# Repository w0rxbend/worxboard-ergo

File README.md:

# worxboard ergo

A split Planck in one curved shell. Forty-eight 1u keys in two wells, opened ten degrees. A full-width palm rest, a memory LCD between the wells, and three places to plug in one USB-C cable. Cherry MX or Kailh Choc v1.

**[Product page](https://w0rxbend.github.io/worxboard-ergo/)** · **[3D print guide](docs/printing.md)** · **[Releases](https://github.com/w0rxbend/worxboard-ergo/releases)**

> [!WARNING]
> **Revision A0 is an engineering preview.** You can print the case. You cannot order the PCB: it has no copper tracks. No keyboard has been built, and the firmware has never run on a board. The pictures are renders of the design.

## What you can do today

| You want to | Start here | State |
|---|---|---|
| See the design | [Product page](https://w0rxbend.github.io/worxboard-ergo/) | Renders of the CAD model |
| Print the case | [3D print guide](docs/printing.md) | Watertight meshes. Nothing printed yet |
| Mill the case | [CNC traveler](docs/cnc.md) | STEP geometry. No toolpath |
| Read the circuit | [Electrical notes](docs/electrical.md) | Schematic and placed parts. **Zero tracks** |
| Build the firmware | [Firmware notes](docs/firmware.md) | Compiles. Never flashed to hardware |
| Order a PCB | — | **Blocked.** See [verification](docs/verification.md) |

## The design

| | |
|---|---|
| Layout | 48 ortholinear keys, two blocks of 4 × 6, every key 1u. Numbers and F-keys on the Lower layer |
| Shell | 303 × 223 mm. A curved outline, an open slot between the wells, a flush top cover |
| Ergonomics | 10° splay, 67 mm palm rest, flat stance, 6.7° negative tilt on an optional magnetic riser |
| Switches | Cherry MX compatible with a 1.5 mm plate, or Kailh Choc v1 with a 1.2 mm plate. Hot-swap sockets |
| Controller | Bare RP2040 with 16 MiB flash, reset, BOOT, and SWD |
| Cable | Three USB-C positions, one host at a time. No battery, no radio |
| Display | 160 × 68 memory LCD that names the active layer |
| Firmware | ZMK at a pinned revision |

Both wells sit on one flat board, so the keys do not tent. The three USB-C jacks are alternative cable positions, not a hub.

## Print the case

1. Choose [MX](cad/exports/mx) or [Choc v1](cad/exports/choc). The parts do not mix.
2. Choose whole parts (350 mm class bed) or split halves (about 235 mm).
3. Print the four test pieces, then the chassis, plate, top cover, and palm rest.

The full steps, orientation, settings, and screw list are in the [3D print guide](docs/printing.md).

## Repository map

| Path | What it holds |
|---|---|
| [`layout/model.py`](layout/model.py) | Source of truth for key positions, key order, and shared holes |
| [`cad/model.py`](cad/model.py) | Parametric case model (build123d) |
| [`cad/exports/`](cad/exports) | STEP, STL, 3MF, and FreeCAD files for both switch families |
| [`pcb/`](pcb) | KiCad 10 projects, generator scripts, ERC and DRC reports |
| [`firmware/`](firmware) | ZMK board definition, USB port selector, compiled UF2 |
| [`site/`](site) | Product page, published with GitHub Pages |
| [`docs/`](docs/README.md) | Guides, design record, verification, roadmap |
| [`tools/`](tools) | Generators and checks behind the `make` targets |
| [`tests/`](tests) | Geometry and contract tests |

## Reproduce the files

Install [uv](https://docs.astral.sh/uv/), Docker, and FreeCAD 1.1.x.

```sh
git clone --recurse-submodules https://github.com/w0rxbend/worxboard-ergo.git
cd worxboard-ergo
uv sync --locked
make generate       # layout drawing and ZMK keymap
make cad            # STEP, STL, 3MF, solid and fit checks
make native         # FreeCAD save and reopen
make test
make pcb            # KiCad boards and ERC/DRC reports. Does not route
make firmware       # pinned ZMK image
make manifest       # checksums
make check-fabrication   # fails on purpose at A0
```

`make check-fabrication` stays red until both boards are routed, reviewed, and tested on hardware. Tool versions are pinned in [`toolchain.lock.json`](toolchain.lock.json) and `uv.lock`.

To redraw the product renders (Blender's path tracer as a Python module, about 30 minutes on 16 CPU threads) and the laser artwork for the signature:

```sh
uv run --no-project --python 3.13 --with bpy==5.3.0 --with build123d==0.13.0 \
    --with shapely==2.2.0 --with pillow==13.0.0 --with imagequant==1.1.6 python -m tools.render
make laser
```

## Status and next steps

The next gate is [A1, electrical and mechanical review](docs/roadmap.md). The main open work:

- Route both PCBs. Turn the USB jacks to face the rear wall and move the parts that sit under the plate.
- Print the test pieces and measure them.
- Review USB power and the J6/J7 flashing override on real hardware.

The evidence for every claim is in [verification](docs/verification.md). Changes per release are in the [changelog](CHANGELOG.md).

## License

Original project work is GPL-3.0-or-later. ZMK, the reference tree, and third-party footprints keep their own notices. See [THIRD_PARTY.md](THIRD_PARTY.md).

This is an independent project. It is not affiliated with Microsoft, System76, or OLKB. The [System76 Launch](https://github.com/system76/launch) tree is a pinned [reference submodule](references/system76-launch); [feature coverage](docs/launch-coverage.md) records the differences.

The product page sets [Outfit](https://github.com/Outfitio/Outfit-Fonts) under the SIL Open Font License. The license text ships in [site/fonts](site/fonts).

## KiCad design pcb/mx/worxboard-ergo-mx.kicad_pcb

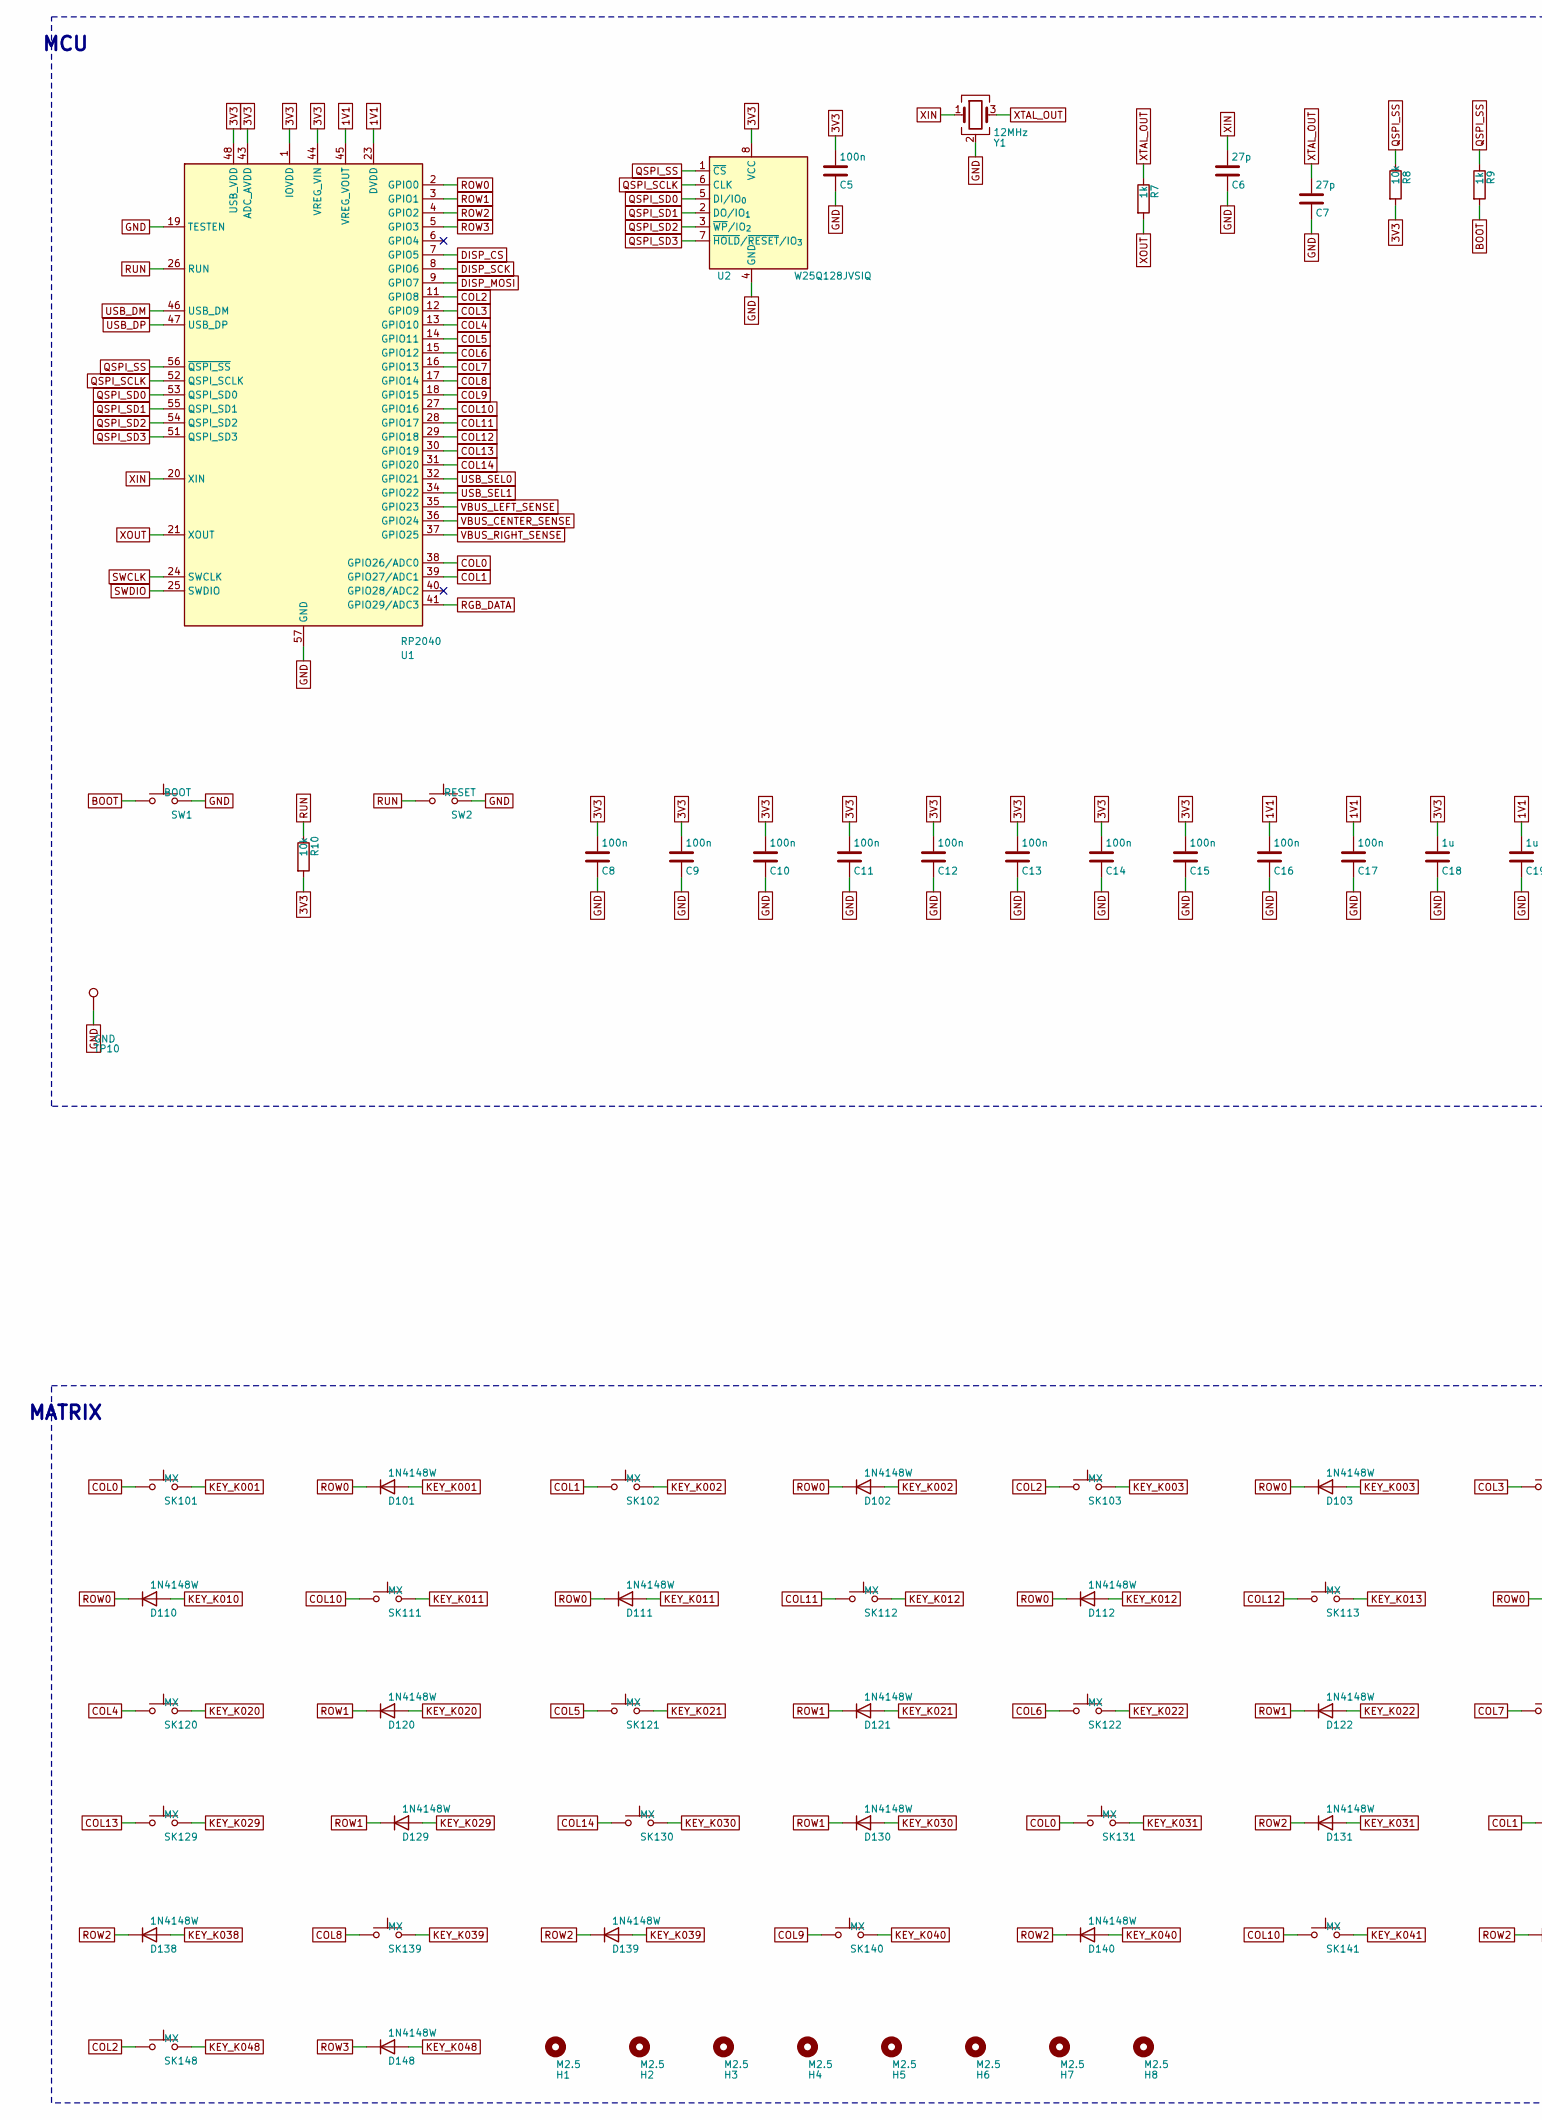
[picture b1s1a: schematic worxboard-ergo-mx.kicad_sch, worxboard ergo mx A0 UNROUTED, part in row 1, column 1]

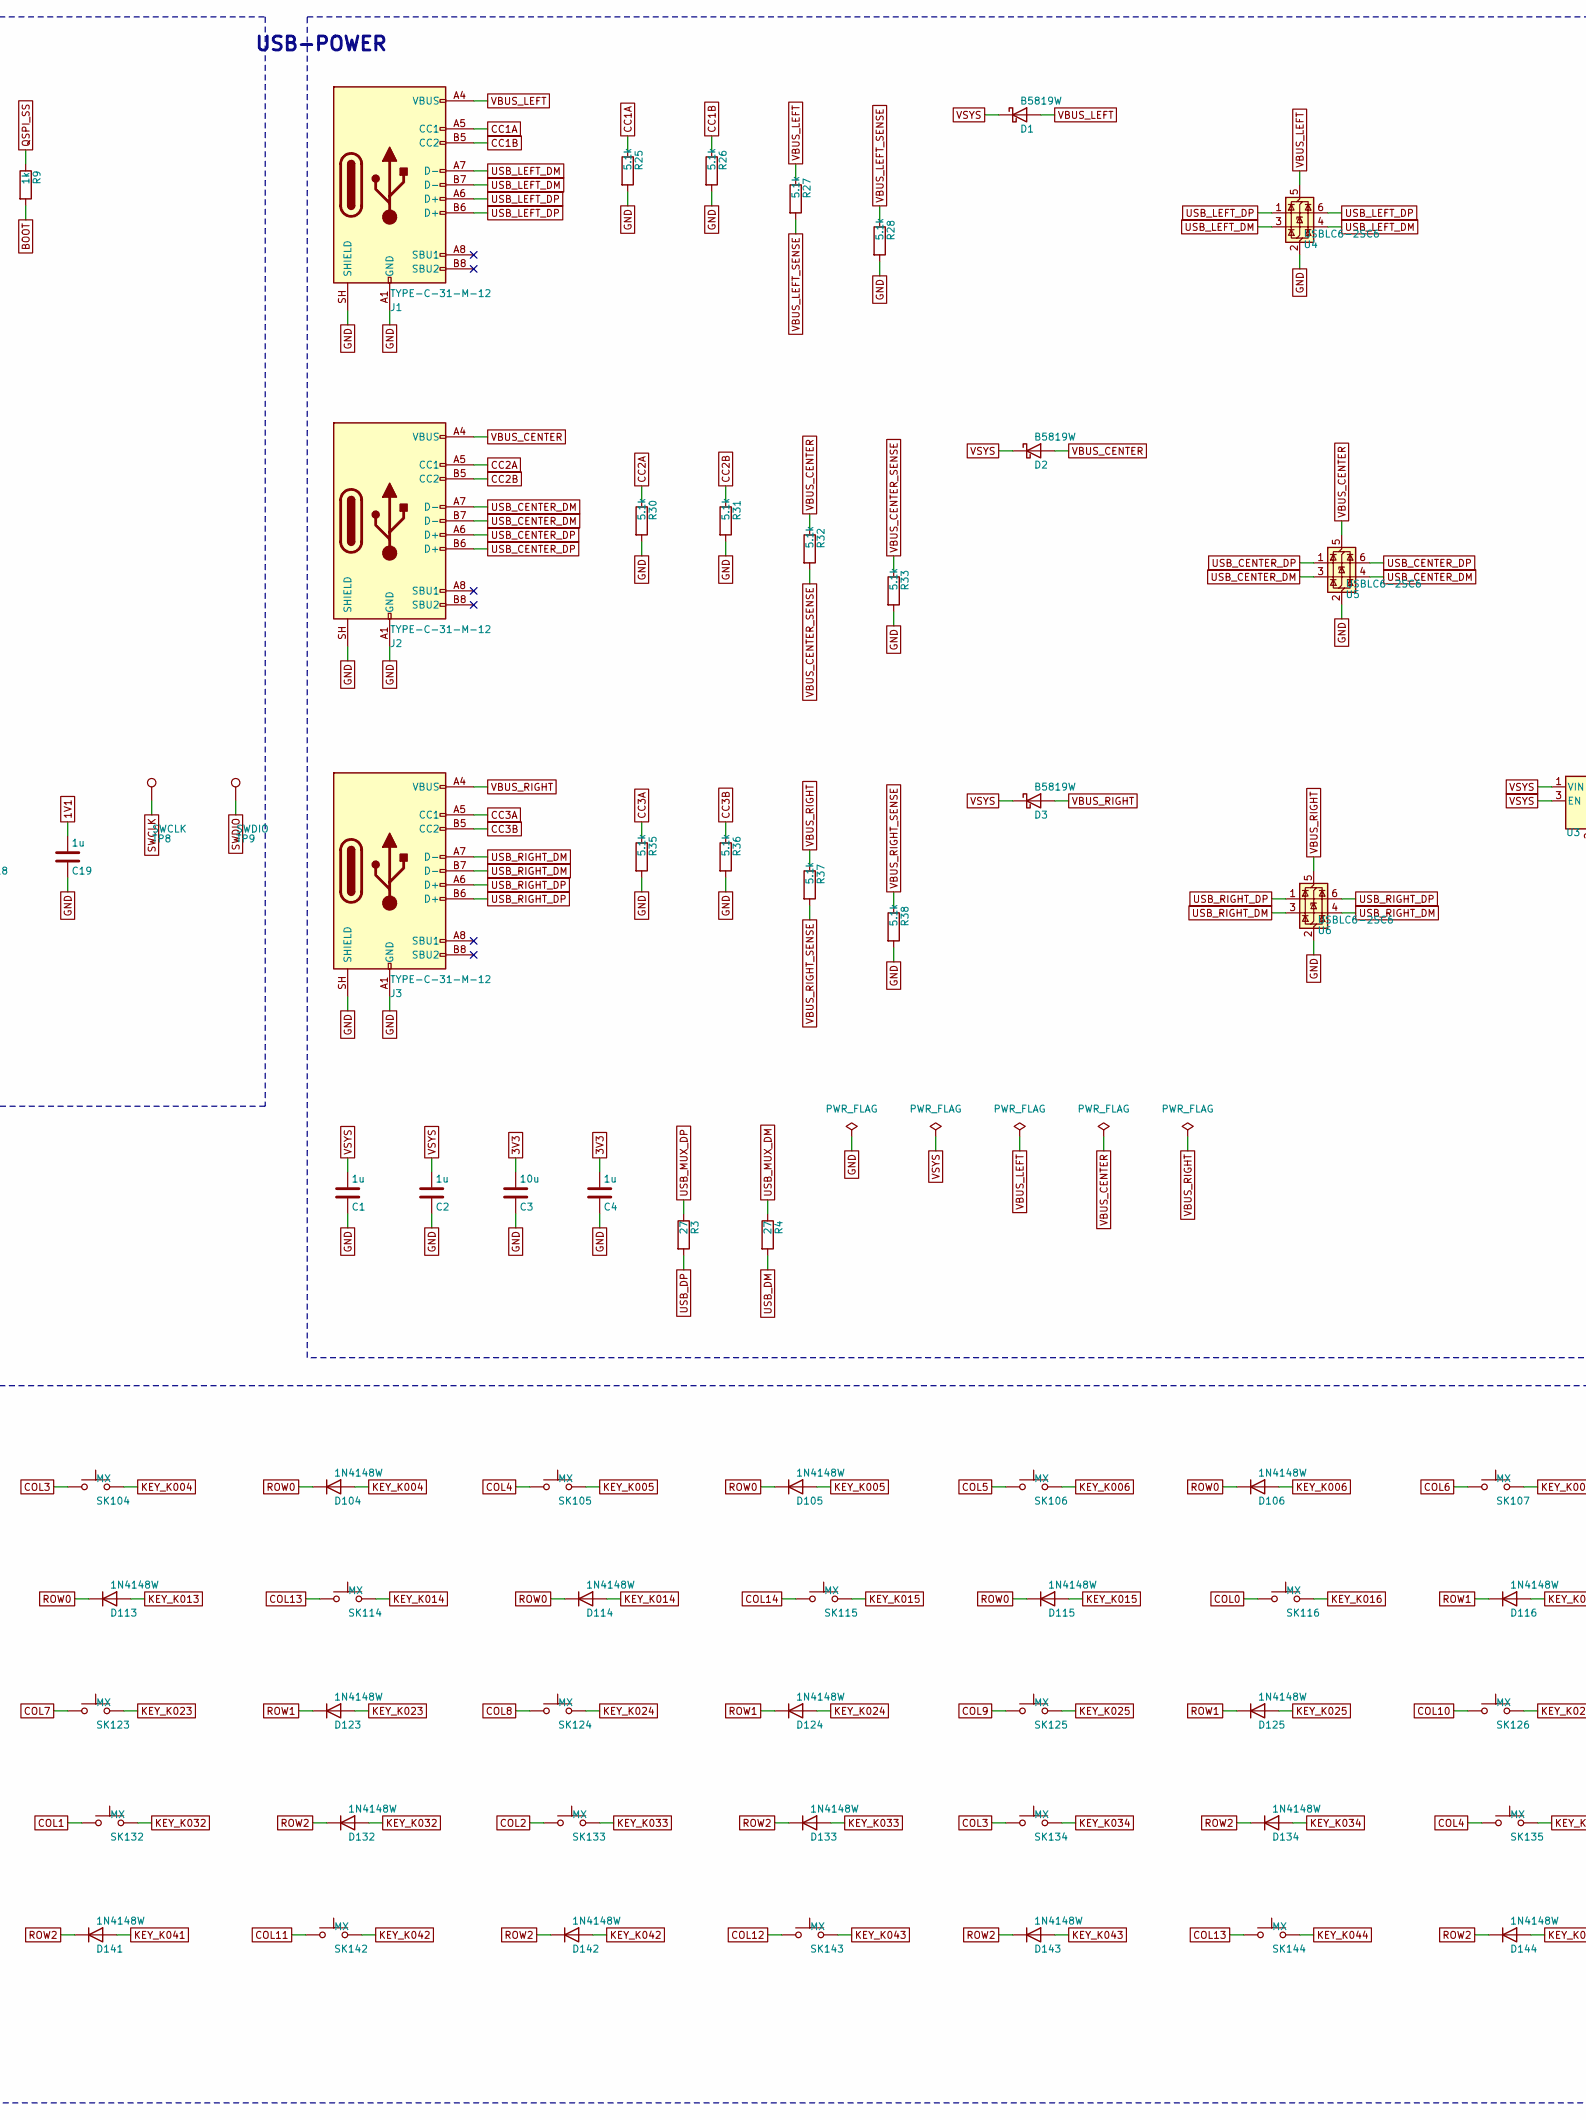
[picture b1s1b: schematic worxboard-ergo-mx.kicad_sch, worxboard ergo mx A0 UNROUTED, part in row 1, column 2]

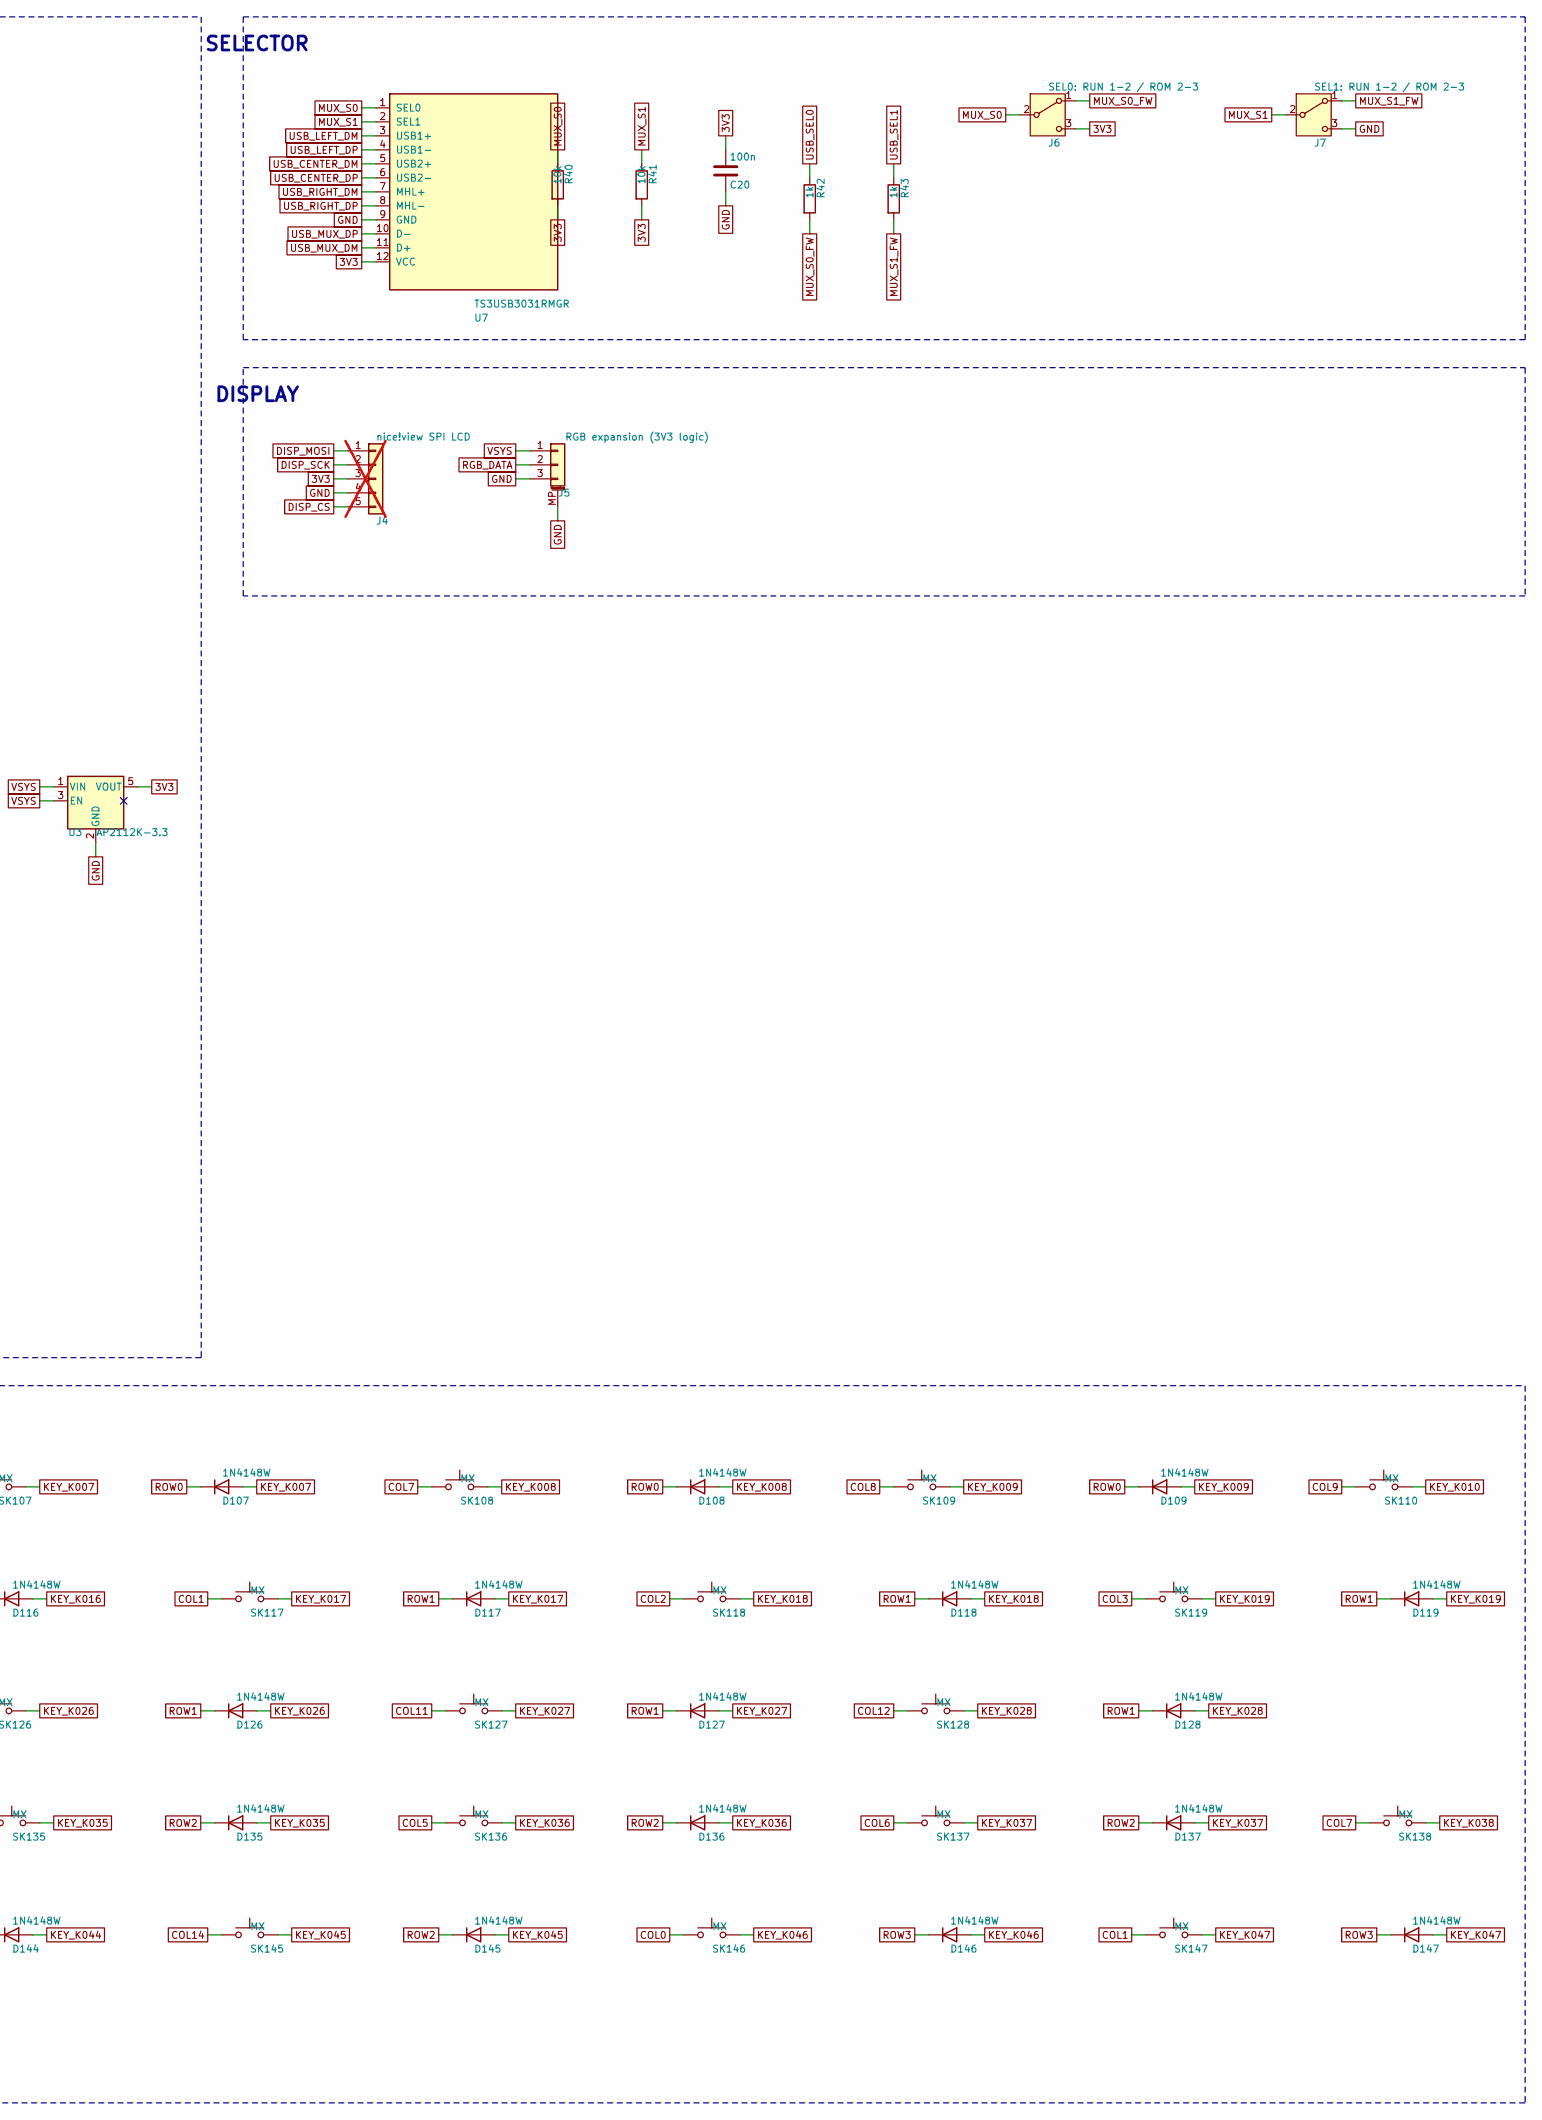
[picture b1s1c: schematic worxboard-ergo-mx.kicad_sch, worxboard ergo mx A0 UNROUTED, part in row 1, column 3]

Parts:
C1, C2, C4, C18, C19: 1u; C_0402_1005Metric; LCSC C52923
C3: 10u; C_0402_1005Metric; LCSC C15525
C5, C8, C9, C10, C11, C12, C13, C14, C15, C16, C17, C20: 100n; C_0402_1005Metric; LCSC C1525
C6, C7: 27p; C_0402_1005Metric; LCSC C1557
D1, D2, D3: B5819W; D_SOD-123; LCSC C8598
D101, D102, D103, D104, D105, D106, D107, D108, D109, D110, D111, D112, D113, D114, D115, D116, D117, D118, D119, D120, D121, D122, D123, D124, D125, D126, D127, D128, D129, D130, D131, D132, D133, D134, D135, D136, D137, D138, D139, D140, D141, D142, D143, D144, D145, D146, D147, D148: 1N4148W; D_SOD-123; LCSC C81598
H1, H2, H3, H4, H5, H6, H7, H8: M2.5; MountingHole_2.7mm_M2.5
J1, J2, J3: TYPE-C-31-M-12; USB_C_Receptacle_HRO_TYPE-C-31-M-12; LCSC C165948
J4: nice!view SPI LCD; PinSocket_1x05_P2.54mm_Vertical_H5.0mm; not fitted
J5: RGB expansion (3V3 logic); JST_SH_SM03B-SRSS-TB_1x03-1MP_P1.00mm_Horizontal; LCSC C160403
J6: SEL0: RUN 1-2 / ROM 2-3; SW_SPDT_PCM12; LCSC C221841
J7: SEL1: RUN 1-2 / ROM 2-3; SW_SPDT_PCM12; LCSC C221841
R3, R4: 27; R_0402_1005Metric; LCSC C2909343
R7, R9, R42, R43: 1k; R_0402_1005Metric; LCSC C11702
R8, R10, R40, R41: 10k; R_0402_1005Metric; LCSC C25744
R25, R26, R27, R28, R30, R31, R32, R33, R35, R36, R37, R38: 5.1k; R_0402_1005Metric; LCSC C25905
SK101, SK102, SK103, SK104, SK105, SK106, SK107, SK108, SK109, SK110, SK111, SK112, SK113, SK114, SK115, SK116, SK117, SK118, SK119, SK120, SK121, SK122, SK123, SK124, SK125, SK126, SK127, SK128, SK129, SK130, SK131, SK132, SK133, SK134, SK135, SK136, SK137, SK138, SK139, SK140, SK141, SK142, SK143, SK144, SK145, SK146, SK147, SK148: MX; SW_MX_Hotswap_Kailh; LCSC C2803348
SW1: BOOT; SW_SPST_TS-1088-xR020; LCSC C455280
SW2: RESET; SW_SPST_TS-1088-xR020; LCSC C455280
TP8: SWCLK; TestPoint_Pad_D1.0mm
TP9: SWDIO; TestPoint_Pad_D1.0mm
TP10: GND; TestPoint_Pad_D1.0mm
U1: RP2040; QFN-56-1EP_7x7mm_P0.4mm_EP3.2x3.2mm; LCSC C2040
U2: W25Q128JVSIQ; SOIC-8_5.3x5.3mm_P1.27mm; LCSC C97521
U3: AP2112K-3.3; SOT-23-5; LCSC C51118
U4, U5, U6: USBLC6-2SC6; SOT-23-6; LCSC C7519
U7: TS3USB3031RMGR; Texas_RMG0012A_WQFN-12_1.8x1.8mm_P0.4mm; LCSC C2652459
Y1: 12MHz; Crystal_SMD_3225-4Pin_3.2x2.5mm; LCSC C49304726

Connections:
1V1: C16.1, C17.1, C19.1, U1.23 (DVDD), U1.45 (VREG_VOUT), U1.50 (DVDD)
3V3: C3.1, C4.1, C5.1, C8.1, C9.1, C10.1, C11.1, C12.1, C13.1, C14.1, C15.1, C18.1, C20.1, J4.3, J6.3 (C), R8.2, R10.2, R40.2, R41.2, U1.1 (IOVDD), U1.10 (IOVDD), U1.22 (IOVDD), U1.33 (IOVDD), U1.42 (IOVDD), U1.43 (ADC_AVDD), U1.44 (VREG_VIN), U1.48 (USB_VDD), U1.49 (IOVDD), U2.8 (VCC), U3.5 (VOUT), U7.12 (VCC)
BOOT: R9.2, SW1.1
CC1A: J1.A5 (CC1), R25.1
CC1B: J1.B5 (CC2), R26.1
CC2A: J2.A5 (CC1), R30.1
CC2B: J2.B5 (CC2), R31.1
CC3A: J3.A5 (CC1), R35.1
CC3B: J3.B5 (CC2), R36.1
COL0: SK101.1, SK116.1, SK131.1, SK146.1, U1.38 (GPIO26/ADC0)
COL1: SK102.1, SK117.1, SK132.1, SK147.1, U1.39 (GPIO27/ADC1)
COL2: SK103.1, SK118.1, SK133.1, SK148.1, U1.11 (GPIO8)
COL3: SK104.1, SK119.1, SK134.1, U1.12 (GPIO9)
COL4: SK105.1, SK120.1, SK135.1, U1.13 (GPIO10)
COL5: SK106.1, SK121.1, SK136.1, U1.14 (GPIO11)
COL6: SK107.1, SK122.1, SK137.1, U1.15 (GPIO12)
COL7: SK108.1, SK123.1, SK138.1, U1.16 (GPIO13)
COL8: SK109.1, SK124.1, SK139.1, U1.17 (GPIO14)
COL9: SK110.1, SK125.1, SK140.1, U1.18 (GPIO15)
COL10: SK111.1, SK126.1, SK141.1, U1.27 (GPIO16)
COL11: SK112.1, SK127.1, SK142.1, U1.28 (GPIO17)
COL12: SK113.1, SK128.1, SK143.1, U1.29 (GPIO18)
COL13: SK114.1, SK129.1, SK144.1, U1.30 (GPIO19)
COL14: SK115.1, SK130.1, SK145.1, U1.31 (GPIO20)
DISP_CS: J4.5, U1.7 (GPIO5)
DISP_MOSI: J4.1, U1.9 (GPIO7)
DISP_SCK: J4.2, U1.8 (GPIO6)
GND: C1.2, C2.2, C3.2, C4.2, C5.2, C6.2, C7.2, C8.2, C9.2, C10.2, C11.2, C12.2, C13.2, C14.2, C15.2, C16.2, C17.2, C18.2, C19.2, C20.2, J1.A1 (GND), J1.A12 (GND), J1.B1 (GND), J1.B12 (GND), J1.SH (SHIELD), J2.A1 (GND), J2.A12 (GND), J2.B1 (GND), J2.B12 (GND), J2.SH (SHIELD), J3.A1 (GND), J3.A12 (GND), J3.B1 (GND), J3.B12 (GND), J3.SH (SHIELD), J4.4, J5.3, J5.MP (MountPin), J7.3 (C), R25.2, R26.2, R28.2, R30.2, R31.2, R33.2, R35.2, R36.2, R38.2, SW1.2, SW2.2, TP10.1, U1.19 (TESTEN), U1.57 (GND), U2.4 (GND), U3.2 (GND), U4.2 (GND), U5.2 (GND), U6.2 (GND), U7.9 (GND), Y1.2 (G), Y1.4 (G)
KEY_K001: D101.2 (A), SK101.2
KEY_K002: D102.2 (A), SK102.2
KEY_K003: D103.2 (A), SK103.2
KEY_K004: D104.2 (A), SK104.2
KEY_K005: D105.2 (A), SK105.2
KEY_K006: D106.2 (A), SK106.2
KEY_K007: D107.2 (A), SK107.2
KEY_K008: D108.2 (A), SK108.2
KEY_K009: D109.2 (A), SK109.2
KEY_K010: D110.2 (A), SK110.2
KEY_K011: D111.2 (A), SK111.2
KEY_K012: D112.2 (A), SK112.2
KEY_K013: D113.2 (A), SK113.2
KEY_K014: D114.2 (A), SK114.2
KEY_K015: D115.2 (A), SK115.2
KEY_K016: D116.2 (A), SK116.2
KEY_K017: D117.2 (A), SK117.2
KEY_K018: D118.2 (A), SK118.2
KEY_K019: D119.2 (A), SK119.2
KEY_K020: D120.2 (A), SK120.2
KEY_K021: D121.2 (A), SK121.2
KEY_K022: D122.2 (A), SK122.2
KEY_K023: D123.2 (A), SK123.2
KEY_K024: D124.2 (A), SK124.2
KEY_K025: D125.2 (A), SK125.2
KEY_K026: D126.2 (A), SK126.2
KEY_K027: D127.2 (A), SK127.2
KEY_K028: D128.2 (A), SK128.2
KEY_K029: D129.2 (A), SK129.2
KEY_K030: D130.2 (A), SK130.2
KEY_K031: D131.2 (A), SK131.2
KEY_K032: D132.2 (A), SK132.2
KEY_K033: D133.2 (A), SK133.2
KEY_K034: D134.2 (A), SK134.2
KEY_K035: D135.2 (A), SK135.2
KEY_K036: D136.2 (A), SK136.2
KEY_K037: D137.2 (A), SK137.2
KEY_K038: D138.2 (A), SK138.2
KEY_K039: D139.2 (A), SK139.2
KEY_K040: D140.2 (A), SK140.2
KEY_K041: D141.2 (A), SK141.2
KEY_K042: D142.2 (A), SK142.2
KEY_K043: D143.2 (A), SK143.2
KEY_K044: D144.2 (A), SK144.2
KEY_K045: D145.2 (A), SK145.2
KEY_K046: D146.2 (A), SK146.2
KEY_K047: D147.2 (A), SK147.2
KEY_K048: D148.2 (A), SK148.2
MUX_S0: J6.2 (B), R40.1, U7.1 (SEL0)
MUX_S0_FW: J6.1 (A), R42.2
MUX_S1: J7.2 (B), R41.1, U7.2 (SEL1)
MUX_S1_FW: J7.1 (A), R43.2
QSPI_SCLK: U1.52 (QSPI_SCLK), U2.6 (CLK)
QSPI_SD0: U1.53 (QSPI_SD0), U2.5 (DI/IO_{0})
QSPI_SD1: U1.55 (QSPI_SD1), U2.2 (DO/IO_{1})
QSPI_SD2: U1.54 (QSPI_SD2), U2.3 (~WP/IO_{2})
QSPI_SD3: U1.51 (QSPI_SD3), U2.7 (~HOLD/~RESET/IO_{3})
QSPI_SS: R8.1, R9.1, U1.56 (~QSPI_SS), U2.1 (~CS)
RGB_DATA: J5.2, U1.41 (GPIO29/ADC3)
ROW0: D101.1 (K), D102.1 (K), D103.1 (K), D104.1 (K), D105.1 (K), D106.1 (K), D107.1 (K), D108.1 (K), D109.1 (K), D110.1 (K), D111.1 (K), D112.1 (K), D113.1 (K), D114.1 (K), D115.1 (K), U1.2 (GPIO0)
ROW1: D116.1 (K), D117.1 (K), D118.1 (K), D119.1 (K), D120.1 (K), D121.1 (K), D122.1 (K), D123.1 (K), D124.1 (K), D125.1 (K), D126.1 (K), D127.1 (K), D128.1 (K), D129.1 (K), D130.1 (K), U1.3 (GPIO1)
ROW2: D131.1 (K), D132.1 (K), D133.1 (K), D134.1 (K), D135.1 (K), D136.1 (K), D137.1 (K), D138.1 (K), D139.1 (K), D140.1 (K), D141.1 (K), D142.1 (K), D143.1 (K), D144.1 (K), D145.1 (K), U1.4 (GPIO2)
ROW3: D146.1 (K), D147.1 (K), D148.1 (K), U1.5 (GPIO3)
RUN: R10.1, SW2.1, U1.26 (RUN)
SWCLK: TP8.1, U1.24 (SWCLK)
SWDIO: TP9.1, U1.25 (SWDIO)
USB_CENTER_DM: J2.A7 (D-), J2.B7 (D-), U5.3 (I/O2), U5.4 (I/O2), U7.5 (USB2+)
USB_CENTER_DP: J2.A6 (D+), J2.B6 (D+), U5.1 (I/O1), U5.6 (I/O1), U7.6 (USB2-)
USB_DM: R4.2, U1.46 (USB_DM)
USB_DP: R3.2, U1.47 (USB_DP)
USB_LEFT_DM: J1.A7 (D-), J1.B7 (D-), U4.3 (I/O2), U4.4 (I/O2), U7.3 (USB1+)
USB_LEFT_DP: J1.A6 (D+), J1.B6 (D+), U4.1 (I/O1), U4.6 (I/O1), U7.4 (USB1-)
USB_MUX_DM: R4.1, U7.11 (D+)
USB_MUX_DP: R3.1, U7.10 (D-)
USB_RIGHT_DM: J3.A7 (D-), J3.B7 (D-), U6.3 (I/O2), U6.4 (I/O2), U7.7 (MHL+)
USB_RIGHT_DP: J3.A6 (D+), J3.B6 (D+), U6.1 (I/O1), U6.6 (I/O1), U7.8 (MHL-)
USB_SEL0: R42.1, U1.32 (GPIO21)
USB_SEL1: R43.1, U1.34 (GPIO22)
VBUS_CENTER: D2.2 (A), J2.A4 (VBUS), J2.A9 (VBUS), J2.B4 (VBUS), J2.B9 (VBUS), R32.1, U5.5 (VBUS)
VBUS_CENTER_SENSE: R32.2, R33.1, U1.36 (GPIO24)
VBUS_LEFT: D1.2 (A), J1.A4 (VBUS), J1.A9 (VBUS), J1.B4 (VBUS), J1.B9 (VBUS), R27.1, U4.5 (VBUS)
VBUS_LEFT_SENSE: R27.2, R28.1, U1.35 (GPIO23)
VBUS_RIGHT: D3.2 (A), J3.A4 (VBUS), J3.A9 (VBUS), J3.B4 (VBUS), J3.B9 (VBUS), R37.1, U6.5 (VBUS)
VBUS_RIGHT_SENSE: R37.2, R38.1, U1.37 (GPIO25)
VSYS: C1.1, C2.1, D1.1 (K), D2.1 (K), D3.1 (K), J5.1, U3.1 (VIN), U3.3 (EN)
XIN: C6.1, U1.20 (XIN), Y1.1
XOUT: R7.2, U1.21 (XOUT)
XTAL_OUT: C7.1, R7.1, Y1.3

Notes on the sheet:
MCU
USB-POWER
SELECTOR
DISPLAY
MATRIX

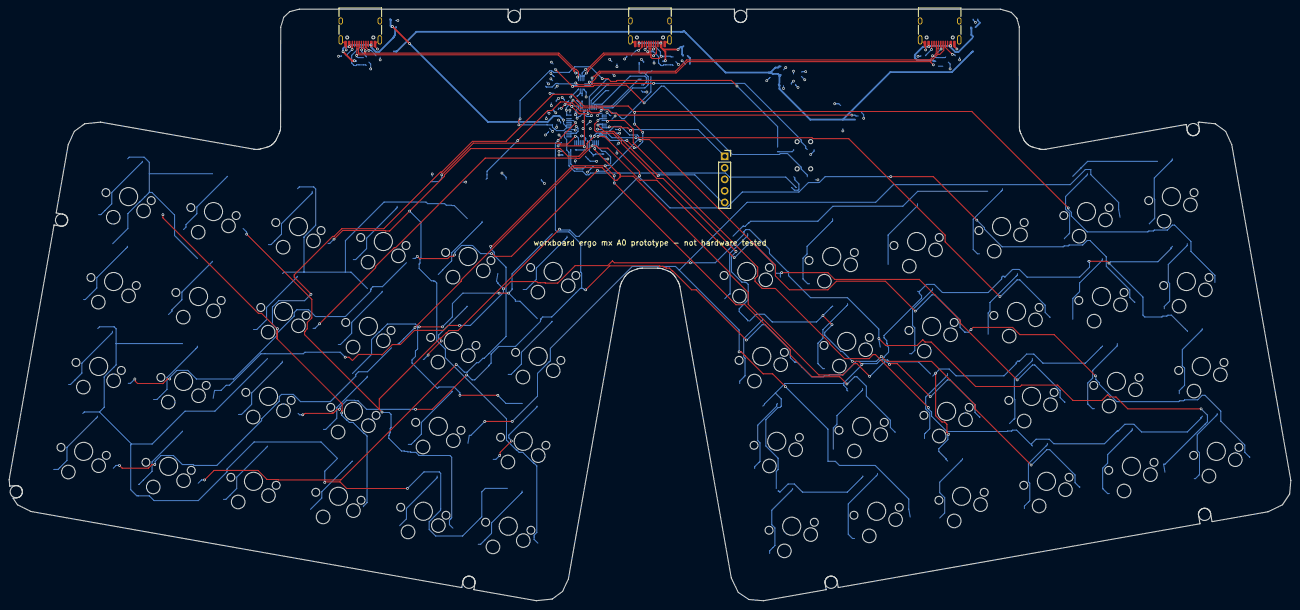
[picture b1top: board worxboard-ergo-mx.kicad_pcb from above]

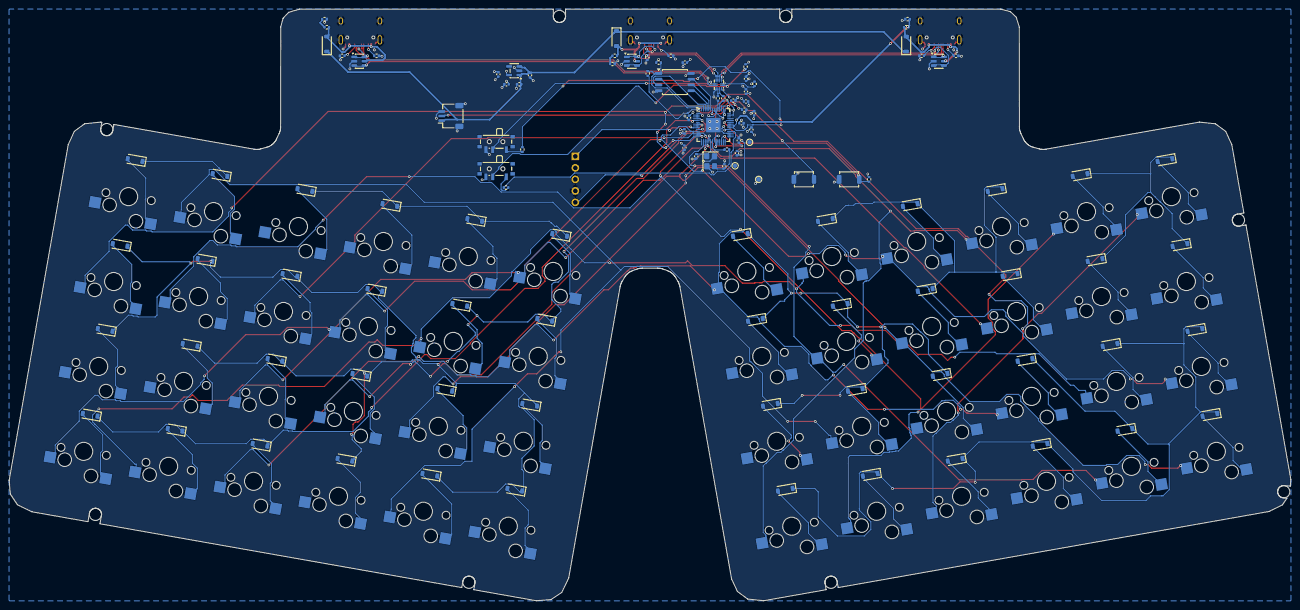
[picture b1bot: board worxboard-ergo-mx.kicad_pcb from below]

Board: 4 copper layers, 283.1 x 130.7 mm, 169 parts (157 on the bottom side), 116 nets.

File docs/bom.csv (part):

variant,reference,value,footprint,manufacturer,mpn,LCSC_reference_only,group,fitted_by,status
mx,U1,RP2040,Package_DFN_QFN:QFN-56-1EP_7x7mm_P0.4mm_EP3.2x3.2mm,Raspberry Pi,RP2040,C2040,MCU,assembler,MPN_READ_2026-11-13_STOCK_AND_PRICE_UNKNOWN
mx,U2,W25Q128JVSIQ,Package_SO:SOIC-8_5.3x5.3mm_P1.27mm,Winbond,W25Q128JVSIQ,C97521,MCU,assembler,MPN_READ_2026-11-13_STOCK_AND_PRICE_UNKNOWN
mx,C5,100n,Capacitor_SMD:C_0402_1005Metric,Samsung Electro-Mechanics,CL05B104KO5NNNC,C1525,MCU,assembler,MPN_READ_2026-11-13_STOCK_AND_PRICE_UNKNOWN
mx,Y1,12MHz,Crystal:Crystal_SMD_3225-4Pin_3.2x2.5mm,YXC,XL2EL89CRI-111YLC-12M,C49304726,MCU,assembler,MPN_READ_2026-11-13_STOCK_AND_PRICE_UNKNOWN
mx,R7,1k,Resistor_SMD:R_0402_1005Metric,UNI-ROYAL,0402WGF1001TCE,C11702,MCU,assembler,MPN_READ_2026-11-13_STOCK_AND_PRICE_UNKNOWN
mx,C6,27p,Capacitor_SMD:C_0402_1005Metric,Fenghua,0402CG270J500NT,C1557,MCU,assembler,MPN_READ_2026-11-13_STOCK_AND_PRICE_UNKNOWN
mx,C7,27p,Capacitor_SMD:C_0402_1005Metric,Fenghua,0402CG270J500NT,C1557,MCU,assembler,MPN_READ_2026-11-13_STOCK_AND_PRICE_UNKNOWN
mx,R8,10k,Resistor_SMD:R_0402_1005Metric,UNI-ROYAL,0402WGF1002TCE,C25744,MCU,assembler,MPN_READ_2026-11-13_STOCK_AND_PRICE_UNKNOWN
mx,R9,1k,Resistor_SMD:R_0402_1005Metric,UNI-ROYAL,0402WGF1001TCE,C11702,MCU,assembler,MPN_READ_2026-11-13_STOCK_AND_PRICE_UNKNOWN
mx,SW1,BOOT,Button_Switch_SMD:SW_SPST_TS-1088-xR020,XUNPU,TS-1088R-02026,C455280,MCU,assembler,MPN_READ_2026-11-13_STOCK_AND_PRICE_UNKNOWN
mx,R10,10k,Resistor_SMD:R_0402_1005Metric,UNI-ROYAL,0402WGF1002TCE,C25744,MCU,assembler,MPN_READ_2026-11-13_STOCK_AND_PRICE_UNKNOWN
mx,SW2,RESET,Button_Switch_SMD:SW_SPST_TS-1088-xR020,XUNPU,TS-1088R-02026,C455280,MCU,assembler,MPN_READ_2026-11-13_STOCK_AND_PRICE_UNKNOWN
mx,C8,100n,Capacitor_SMD:C_0402_1005Metric,Samsung Electro-Mechanics,CL05B104KO5NNNC,C1525,MCU,assembler,MPN_READ_2026-11-13_STOCK_AND_PRICE_UNKNOWN
mx,C9,100n,Capacitor_SMD:C_0402_1005Metric,Samsung Electro-Mechanics,CL05B104KO5NNNC,C1525,MCU,assembler,MPN_READ_2026-11-13_STOCK_AND_PRICE_UNKNOWN
mx,C10,100n,Capacitor_SMD:C_0402_1005Metric,Samsung Electro-Mechanics,CL05B104KO5NNNC,C1525,MCU,assembler,MPN_READ_2026-11-13_STOCK_AND_PRICE_UNKNOWN
mx,C11,100n,Capacitor_SMD:C_0402_1005Metric,Samsung Electro-Mechanics,CL05B104KO5NNNC,C1525,MCU,assembler,MPN_READ_2026-11-13_STOCK_AND_PRICE_UNKNOWN
mx,C12,100n,Capacitor_SMD:C_0402_1005Metric,Samsung Electro-Mechanics,CL05B104KO5NNNC,C1525,MCU,assembler,MPN_READ_2026-11-13_STOCK_AND_PRICE_UNKNOWN
mx,C13,100n,Capacitor_SMD:C_0402_1005Metric,Samsung Electro-Mechanics,CL05B104KO5NNNC,C1525,MCU,assembler,MPN_READ_2026-11-13_STOCK_AND_PRICE_UNKNOWN
mx,C14,100n,Capacitor_SMD:C_0402_1005Metric,Samsung Electro-Mechanics,CL05B104KO5NNNC,C1525,MCU,assembler,MPN_READ_2026-11-13_STOCK_AND_PRICE_UNKNOWN
mx,C15,100n,Capacitor_SMD:C_0402_1005Metric,Samsung Electro-Mechanics,CL05B104KO5NNNC,C1525,MCU,assembler,MPN_READ_2026-11-13_STOCK_AND_PRICE_UNKNOWN
mx,C16,100n,Capacitor_SMD:C_0402_1005Metric,Samsung Electro-Mechanics,CL05B104KO5NNNC,C1525,MCU,assembler,MPN_READ_2026-11-13_STOCK_AND_PRICE_UNKNOWN
mx,C17,100n,Capacitor_SMD:C_0402_1005Metric,Samsung Electro-Mechanics,CL05B104KO5NNNC,C1525,MCU,assembler,MPN_READ_2026-11-13_STOCK_AND_PRICE_UNKNOWN
mx,C18,1u,Capacitor_SMD:C_0402_1005Metric,Samsung Electro-Mechanics,CL05A105KA5NQNC,C52923,MCU,assembler,MPN_READ_2026-11-13_STOCK_AND_PRICE_UNKNOWN
mx,C19,1u,Capacitor_SMD:C_0402_1005Metric,Samsung Electro-Mechanics,CL05A105KA5NQNC,C52923,MCU,assembler,MPN_READ_2026-11-13_STOCK_AND_PRICE_UNKNOWN
mx,J1,TYPE-C-31-M-12,Connector_USB:USB_C_Receptacle_HRO_TYPE-C-31-M-12,Korean Hroparts Elec,TYPE-C-31-M-12,C165948,USB-POWER,assembler,MPN_READ_2026-11-13_STOCK_AND_PRICE_UNKNOWN
mx,R25,5.1k,Resistor_SMD:R_0402_1005Metric,UNI-ROYAL,0402WGF5101TCE,C25905,USB-POWER,assembler,MPN_READ_2026-11-13_STOCK_AND_PRICE_UNKNOWN
mx,R26,5.1k,Resistor_SMD:R_0402_1005Metric,UNI-ROYAL,0402WGF5101TCE,C25905,USB-POWER,assembler,MPN_READ_2026-11-13_STOCK_AND_PRICE_UNKNOWN
mx,R27,5.1k,Resistor_SMD:R_0402_1005Metric,UNI-ROYAL,0402WGF5101TCE,C25905,USB-POWER,assembler,MPN_READ_2026-11-13_STOCK_AND_PRICE_UNKNOWN
mx,R28,5.1k,Resistor_SMD:R_0402_1005Metric,UNI-ROYAL,0402WGF5101TCE,C25905,USB-POWER,assembler,MPN_READ_2026-11-13_STOCK_AND_PRICE_UNKNOWN
mx,D1,B5819W,Diode_SMD:D_SOD-123,JSCJ,B5819W SL,C8598,USB-POWER,assembler,MPN_READ_2026-11-13_STOCK_AND_PRICE_UNKNOWN
mx,U4,USBLC6-2SC6,Package_TO_SOT_SMD:SOT-23-6,STMicroelectronics,USBLC6-2SC6,C7519,USB-POWER,assembler,MPN_READ_2026-11-13_STOCK_AND_PRICE_UNKNOWN
mx,J2,TYPE-C-31-M-12,Connector_USB:USB_C_Receptacle_HRO_TYPE-C-31-M-12,Korean Hroparts Elec,TYPE-C-31-M-12,C165948,USB-POWER,assembler,MPN_READ_2026-11-13_STOCK_AND_PRICE_UNKNOWN
mx,R30,5.1k,Resistor_SMD:R_0402_1005Metric,UNI-ROYAL,0402WGF5101TCE,C25905,USB-POWER,assembler,MPN_READ_2026-11-13_STOCK_AND_PRICE_UNKNOWN
mx,R31,5.1k,Resistor_SMD:R_0402_1005Metric,UNI-ROYAL,0402WGF5101TCE,C25905,USB-POWER,assembler,MPN_READ_2026-11-13_STOCK_AND_PRICE_UNKNOWN
mx,R32,5.1k,Resistor_SMD:R_0402_1005Metric,UNI-ROYAL,0402WGF5101TCE,C25905,USB-POWER,assembler,MPN_READ_2026-11-13_STOCK_AND_PRICE_UNKNOWN
mx,R33,5.1k,Resistor_SMD:R_0402_1005Metric,UNI-ROYAL,0402WGF5101TCE,C25905,USB-POWER,assembler,MPN_READ_2026-11-13_STOCK_AND_PRICE_UNKNOWN
mx,D2,B5819W,Diode_SMD:D_SOD-123,JSCJ,B5819W SL,C8598,USB-POWER,assembler,MPN_READ_2026-11-13_STOCK_AND_PRICE_UNKNOWN
mx,U5,USBLC6-2SC6,Package_TO_SOT_SMD:SOT-23-6,STMicroelectronics,USBLC6-2SC6,C7519,USB-POWER,assembler,MPN_READ_2026-11-13_STOCK_AND_PRICE_UNKNOWN
mx,J3,TYPE-C-31-M-12,Connector_USB:USB_C_Receptacle_HRO_TYPE-C-31-M-12,Korean Hroparts Elec,TYPE-C-31-M-12,C165948,USB-POWER,assembler,MPN_READ_2026-11-13_STOCK_AND_PRICE_UNKNOWN
mx,R35,5.1k,Resistor_SMD:R_0402_1005Metric,UNI-ROYAL,0402WGF5101TCE,C25905,USB-POWER,assembler,MPN_READ_2026-11-13_STOCK_AND_PRICE_UNKNOWN
mx,R36,5.1k,Resistor_SMD:R_0402_1005Metric,UNI-ROYAL,0402WGF5101TCE,C25905,USB-POWER,assembler,MPN_READ_2026-11-13_STOCK_AND_PRICE_UNKNOWN
mx,R37,5.1k,Resistor_SMD:R_0402_1005Metric,UNI-ROYAL,0402WGF5101TCE,C25905,USB-POWER,assembler,MPN_READ_2026-11-13_STOCK_AND_PRICE_UNKNOWN
mx,R38,5.1k,Resistor_SMD:R_0402_1005Metric,UNI-ROYAL,0402WGF5101TCE,C25905,USB-POWER,assembler,MPN_READ_2026-11-13_STOCK_AND_PRICE_UNKNOWN
mx,D3,B5819W,Diode_SMD:D_SOD-123,JSCJ,B5819W SL,C8598,USB-POWER,assembler,MPN_READ_2026-11-13_STOCK_AND_PRICE_UNKNOWN
mx,U6,USBLC6-2SC6,Package_TO_SOT_SMD:SOT-23-6,STMicroelectronics,USBLC6-2SC6,C7519,USB-POWER,assembler,MPN_READ_2026-11-13_STOCK_AND_PRICE_UNKNOWN
mx,U3,AP2112K-3.3,Package_TO_SOT_SMD:SOT-23-5,Diodes Incorporated,AP2112K-3.3TRG1,C51118,USB-POWER,assembler,MPN_READ_2026-11-13_STOCK_AND_PRICE_UNKNOWN
mx,C1,1u,Capacitor_SMD:C_0402_1005Metric,Samsung Electro-Mechanics,CL05A105KA5NQNC,C52923,USB-POWER,assembler,MPN_READ_2026-11-13_STOCK_AND_PRICE_UNKNOWN
mx,C2,1u,Capacitor_SMD:C_0402_1005Metric,Samsung Electro-Mechanics,CL05A105KA5NQNC,C52923,USB-POWER,assembler,MPN_READ_2026-11-13_STOCK_AND_PRICE_UNKNOWN
mx,C3,10u,Capacitor_SMD:C_0402_1005Metric,Samsung Electro-Mechanics,CL05A106MQ5NUNC,C15525,USB-POWER,assembler,MPN_READ_2026-11-13_STOCK_AND_PRICE_UNKNOWN
mx,C4,1u,Capacitor_SMD:C_0402_1005Metric,Samsung Electro-Mechanics,CL05A105KA5NQNC,C52923,USB-POWER,assembler,MPN_READ_2026-11-13_STOCK_AND_PRICE_UNKNOWN
mx,R3,27,Resistor_SMD:R_0402_1005Metric,FOJAN,FRC0402F27R0TS,C2909343,USB-POWER,assembler,MPN_READ_2026-11-13_STOCK_AND_PRICE_UNKNOWN
mx,R4,27,Resistor_SMD:R_0402_1005Metric,FOJAN,FRC0402F27R0TS,C2909343,USB-POWER,assembler,MPN_READ_2026-11-13_STOCK_AND_PRICE_UNKNOWN
mx,U7,TS3USB3031RMGR,Package_DFN_QFN:Texas_RMG0012A_WQFN-12_1.8x1.8mm_P0.4mm,Texas Instruments,TS3USB3031RMGR,C2652459,SELECTOR,assembler,MPN_READ_2026-11-13_STOCK_AND_PRICE_UNKNOWN
mx,R40,10k,Resistor_SMD:R_0402_1005Metric,UNI-ROYAL,0402WGF1002TCE,C25744,SELECTOR,assembler,MPN_READ_2026-11-13_STOCK_AND_PRICE_UNKNOWN
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

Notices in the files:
README.md:
License: GPL-3.0-or-later
